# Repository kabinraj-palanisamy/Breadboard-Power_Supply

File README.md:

# Breadboard Power Supply
A multi-output regulated bench power supply PCB designed in KiCad 10,
intended for prototyping and breadboard use.

## Features
- Dual selectable output rails: fixed 5V (LM7805) and adjustable
  voltage (LM317)
- Output voltage options: 3.3V, 5V, 12V via onboard selector headers
- Barrel jack DC input with slide switch power control
- LED power indicator
- Dual output interfaces: breadboard pin headers + screw terminals

## Tools
KiCad 10.0.1

## Status
Schematic complete — PCB layout in progress

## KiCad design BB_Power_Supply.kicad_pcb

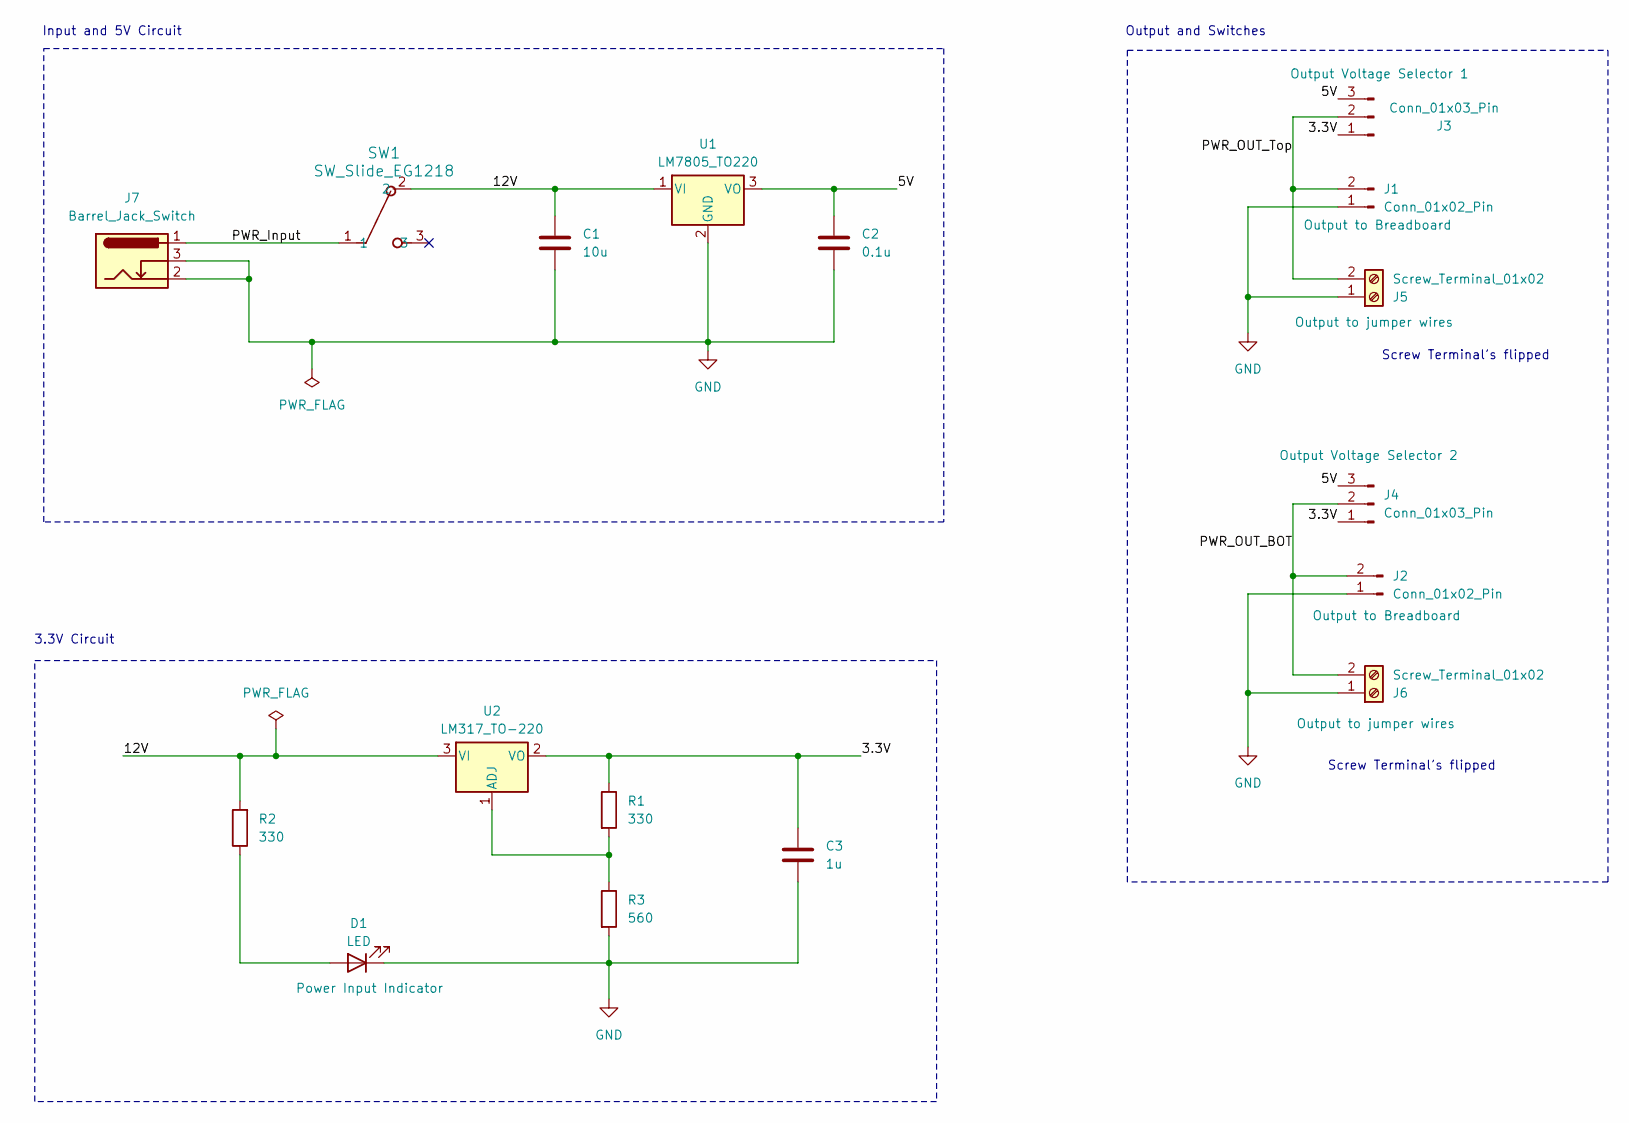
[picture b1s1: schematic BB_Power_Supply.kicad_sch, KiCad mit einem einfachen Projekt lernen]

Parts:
C1: 10u; C_Disc_D3.0mm_W1.6mm_P2.50mm
C2: 0.1u; C_Disc_D3.0mm_W1.6mm_P2.50mm
C3: 1u; C_Disc_D3.0mm_W1.6mm_P2.50mm
D1: LED; LED_D5.0mm
J1, J2: Conn_01x02_Pin; PinHeader_1x02_P2.54mm_Vertical
J3, J4: Conn_01x03_Pin; PinHeader_1x03_P2.54mm_Vertical
J5, J6: Screw_Terminal_01x02; TerminalBlock_MaiXu_MX126-5.0-02P_1x02_P5.00mm
J7: Barrel_Jack_Switch; BarrelJack_Horizontal
R1, R2: 330; R_Axial_DIN0204_L3.6mm_D1.6mm_P7.62mm_Horizontal
R3: 560; R_Axial_DIN0204_L3.6mm_D1.6mm_P7.62mm_Horizontal
SW1: SW_Slide_EG1218
U1: LM7805_TO220; TO-220-3_Vertical
U2: LM317_TO-220; TO-220-3_Vertical

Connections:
/3.3V: C3.1, J3.1, J4.1, R1.1, U2.2 (VO)
/5V: C2.1, J3.3, J4.3, U1.3 (VO)
/12V: C1.1, R2.2, SW1.2, U1.1 (VI), U2.3 (VI)
/PWR_Input: J7.1, SW1.1
/PWR_OUT_BOT: J2.2, J4.2, J6.2
/PWR_OUT_Top: J1.2, J3.2, J5.2
GND: C1.2, C2.2, C3.2, D1.1 (K), J1.1, J2.1, J5.1, J6.1, J7.2, J7.3, R3.2, U1.2 (GND)
unnamed: D1.2 (A), R2.1
unnamed: R1.2, R3.1, U2.1 (ADJ)

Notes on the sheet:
Input and 5V Circuit
3.3V Circuit
Output and Switches
Screw Terminal's flipped

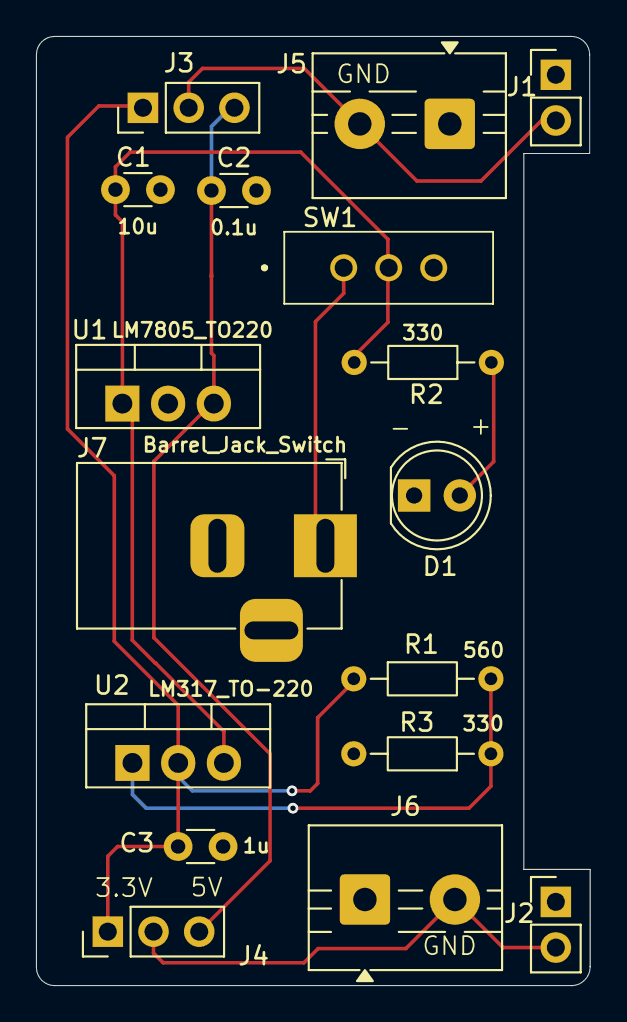
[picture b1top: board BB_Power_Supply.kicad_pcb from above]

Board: 2 copper layers, 30.8 x 52.7 mm, 17 parts (0 on the bottom side), 9 nets.
